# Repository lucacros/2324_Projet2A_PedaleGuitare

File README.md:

# Hi everyone 🖐️ & Welcome to our project: Multi-Effects Guitar Pedal 🎸🎛️

Hello music and technology fans! Welcome to the GitHub showcase for our multi-effects guitar pedal project. Here you'll find details, tools, and resources related to this exciting project. This is an academic project completed in 100 hours by the legendary trio: Luca CROSETTO, Jolan THOMASSET, and Camille LANFREDI

## 📖 Table of contents

- [📌 Présentation](#-présentation)
  - [📅 Management Section](#-management-section)
  - [🛠️ Hardware Section](#-hardware-section)
  - [💻 Software Section](#-software-section)
- [🚀 Contributions](#-contributions)
- [📜 Licence](#-licence)

## 📌 Présentation

Our multi-effects guitar pedal project aims to provide a versatile platform for guitarists, bringing together a variety of sound effects and audio processing tools in a single device. To achieve this, the guitar pedal will feature...

The project is divided into 3 parts: the first one is the project management, the second part is analog part, with the creation of the system's electronic board, and the third is the creation of the various digital audio effects. 
The second is the creation of the various digital audio effects.

## 📅 Management Section

In this section, you'll find everything to do with project management.

[Link to Management.md](Management.md)

## 🛠️ Hardware Section

### Power supply
To obtain these voltage levels, we use several voltage regulators. The first regulator is a switching regulator to go from 12V to 5V and then we use 2 linear regulators to obtain 3.3V and 1.8V. We first use a switching regulator to go from 12V to 5V, because switching regulators are more efficient than linear regulators when the voltage difference between input and output is high. We use linear regulators because they give a very clean output, with a minimum of noise.

We need to supply 2 different voltages: the first +3.3V to supply VDDA (for analogue part) and VDDIO (for Inputs/Outputs) and the second +1.8V to supply VDDD (for digital part).

|   Components   |   Voltages |  Description |
|---    |:-:    |:-    | 
|   VDDIO   |   +3.3V   | Power supply controls the digital I/O levels as well as the output level of LINE outputs. | 
| VDDD   |   +1.8V  | power supply controls the digital I/O levels as well as the output level of LINE outputs   |
|  VDDA  |   +3.3VA   | Power supply is used for the internal analog circuitry including ADC, DAC, LINE inputs, MIC inputs, headphone outputs and reference voltages.|

#### Jack connecting
We use Jack switched for the input and the output of the guitar. The switched Jack allow us to have the choice between a mono-input or a stereo input and a mono-output and a stereo-output. 
When we connect a jack to this connector, the pins SN and TN are disconnected from the pins S and T. It can allow to have 2 connectors to have stereo but still use the 2 input of the codec to have a signal as powerful as a stereo input.
#### Buffer-Button
We use a buffer button to store a part of the sound of the guitar to apply several effects to it. It's one of the several options that offer the granular effect.
When the button is pressed, a signal is sent to the microprocessor. When it receives the signal, the microprocessor stores in the RAM the song it has received for a short time and continuously plays the part stored in the RAM.
#### Potentiometers
We use several potentiometers for all the settings of our effects, the gain, the shape, the reverb ect... All potentiometers are fitted with capacitors to eliminate unwanted noise and high frequencies.

They are 2 versions of the pcb :
| V | Recto | Verso  | Size |
|---|------|-------|-----|
| V1.0|  | | 17 x 10.32 cm |
| V2.0|  | | 10.4 x 9.15 cm |
| V3.0| **WIP**  | **WIP**| 9.71 x 6.76 cm |

As you can see, the first version wasn't optimised. They is a lot of space between components and the design is not very good. That's why we did a new version witch to x2 smaller.

## 💻 Software Section

In this second part you will find everything that concerns the software part of the project. You'll find all the detailed audio effects programs and how they work.

[Link to Software Section](https://github.com/lucacros/2324_Projet2A_PedaleGuitare/tree/Software-Section)

## 🚀 Contributions

We would like to thank each person who helped us and provided support and information, such as:
- M. Nicolas PAPAZOGLOU
- M. Laurent FIACK
- M. Frédéric GERALDO

## 📜 Licence

The project is under the [SI TU VOLES T'ES MORT] license. Refer to the `LICENSE` file for more details.

---
Feel free to star this project (⭐) if you find it interesting!

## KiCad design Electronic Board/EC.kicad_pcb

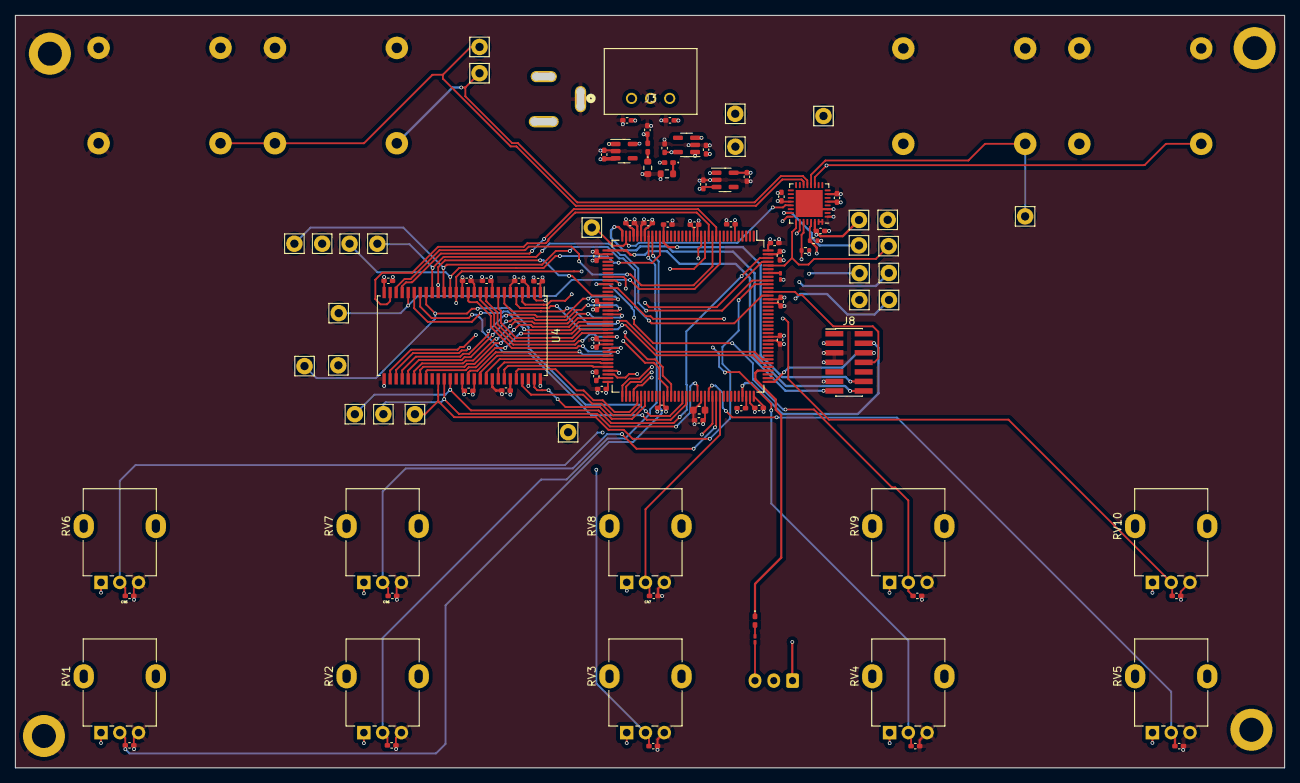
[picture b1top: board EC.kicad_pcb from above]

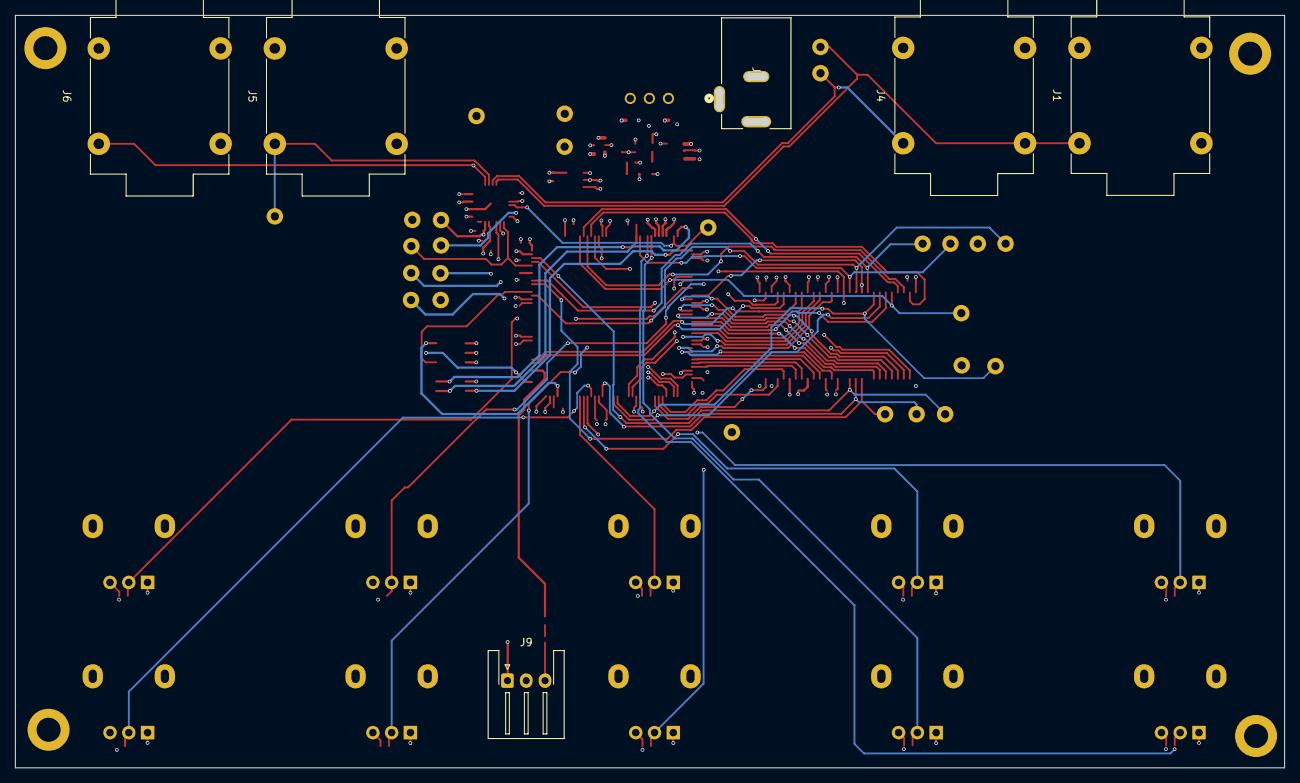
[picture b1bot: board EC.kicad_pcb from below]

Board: 4 copper layers, 169.0 x 100.2 mm, 110 parts (6 on the bottom side), 79 nets.

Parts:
C1: 100uF; C_0402_1005Metric_Pad0.74x0.62mm_HandSolder
C2: 100µF; C_0402_1005Metric_Pad0.74x0.62mm_HandSolder
C3, C4, C5, C6, C7, C8: 1uF; C_0402_1005Metric_Pad0.74x0.62mm_HandSolder
C9, C10, C11, C12, C13, C14, C15, C20, C21, C22, C23, C24, C25, C26, C27, C28, C29, C30, C31, C32, C33, C34, C35, C40, C41, C42, C43, C44, C45, C46, C47, C48, C49, C50, C51, C60: 100nF; C_0402_1005Metric_Pad0.74x0.62mm_HandSolder
C17: 4.7u; C_0603_1608Metric
C18, C19: 2.2uF; C_0402_1005Metric_Pad0.74x0.62mm_HandSolder
D1, D3: RED; LED_0402_1005Metric_Pad0.77x0.64mm_HandSolder
D2: LED; LED_0402_1005Metric_Pad0.77x0.64mm_HandSolder
H1, H2, H3, H4: MountingHole_Pad; MountingHole_3.2mm_M3_DIN965_Pad
J1, J4, J5, J6: NMJ4HCD2; Jack_6.35mm_Neutrik_NMJ4HCD2_Horizontal
J2: 4840.2201; Regulator4840-2201
J3: 173950578; CONN3_950578_WRE_173950578
J8: Conn_02x07_Odd_Even; PinHeader_2x07_P1.27mm_Vertical_SMD
J9: Conn_01x03; JST_XH_S3B-XH-A-1_1x03_P2.50mm_Horizontal
R1, R2: 1k; R_0603_1608Metric
R3: 330; R_0201_0603Metric_Pad0.64x0.40mm_HandSolder
R5, R7: 1.5k; R_0402_1005Metric
R6: 510; R_0201_0603Metric_Pad0.64x0.40mm_HandSolder
RV1, RV2, RV3, RV4, RV5, RV6, RV7, RV8, RV9, RV10: 100k; Potentiometer_Alpha_RD901F-40-00D_Single_Vertical
TP1, TP2, TP3, TP4, TP5, TP6, TP8, TP9, TP10, TP11, TP12, TP13, TP14, TP15, TP16, TP17, TP18, TP19, TP20, TP21, TP22, TP23, TP24, TP25, TP34, TP35: TestPoint; Pin_D1.1mm_L8.5mm_W2.5mm_FlatFork
U1, U2: BU33SD5WG-TR; SOT-23-5
U3: BU18SD2MG-MTR; SOT-23-5
U4: IS42S16400J-xC; TSOP-II-54_22.2x10.16mm_P0.8mm
U6: STM32F446ZCTx; LQFP-144_20x20mm_P0.5mm
U7: SGTL5000XNAA3; QFN-32-1EP_5x5mm_P0.5mm_EP3.6x3.6mm

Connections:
+1V8: C8.1, C51.1, TP4.1, U3.5 (OUT), U7.30 (VDDD)
+3.3V: C4.1, C7.1, C9.1, C10.1, C11.1, C12.1, C13.1, C14.1, C15.1, C17.1, C20.1, C21.1, C22.1, C23.1, C25.1, C26.1, C27.1, C28.1, C29.1, C30.1, C31.1, C32.1, C33.1, C34.1, C35.1, D1.2 (A), J8.3, J9.1, R5.1, R7.1, RV1.1, RV2.1, RV3.1, RV4.1, RV5.1, RV6.1, RV7.1, RV8.1, RV9.1, RV10.1, TP2.1, U1.5 (OUT), U3.1 (IN), U3.3 (STBY), U4.1 (VDD), U4.3 (VDDQ), U4.9 (VDDQ), U4.14 (VDD), U4.27 (VDD), U4.43 (VDDQ), U4.49 (VDDQ), U6.6 (VBAT), U6.17 (VDD), U6.30 (VDD), U6.39 (VDD), U6.52 (VDD), U6.62 (VDD), U6.72 (VDD), U6.84 (VDD), U6.95 (VDDUSB), U6.108 (VDD), U6.121 (VDD), U6.131 (VDD), U6.143 (PDR_ON), U6.144 (VDD), U7.20 (VDDIO)
+3.3VA: C6.1, C24.1, C50.1, D3.2 (A), TP3.1, U2.5 (OUT), U6.33 (VDDA), U7.5 (VDDA)
+5V: C2.1, C3.1, C5.1, J3.3 (Vs), TP1.1, U1.1 (IN), U1.3 (STBY), U2.1 (IN), U2.3 (STBY)
+12V: C1.1, J2.1 (+Ve), J3.1 (+Ve)
/Codec/CK_I2S: TP24.1, U6.74 (PB13), U7.24 (I2S_SCLK)
/Codec/DOUT_I2S: TP22.1, U6.140 (PB9), U7.25 (I2S_DOUT)
/Codec/SCL_I2C: R7.2, TP20.1, U6.69 (PB10), U7.29 (CTRL_CLK)
/Codec/SDA_I2C: R5.2, TP19.1, U6.70 (PB11), U7.27 (CTRL_DATA)
/Codec/SD_I2S: TP21.1, U6.76 (PB15), U7.26 (I2S_DIN)
/Codec/SYS_MCLK: TP18.1, U6.35 (PA1), U7.21 (SYS_MCLK)
/Codec/Ve_guitare_L: J1.T, J4.TN, TP5.1, U7.14 (LINEIN_L)
/Codec/Ve_guitare_R: J4.T, TP34.1, U7.13 (LINEIN_R)
/Codec/Vs_guitare_L: J5.T, TP6.1, U7.12 (LINEOUT_L)
/Codec/Vs_guitare_R: J6.T, TP35.1, U7.11 (LINEOUT_R)
/Codec/WS_I2S: TP23.1, U6.73 (PB12), U7.23 (I2S_LRCLK)
/STM32/A0: TP15.1, U4.23 (A0), U6.10 (PF0)
/STM32/A1: U4.24 (A1), U6.11 (PF1)
/STM32/A2: U4.25 (A2), U6.12 (PF2)
/STM32/A3: U4.26 (A3), U6.13 (PF3)
/STM32/A4: U4.29 (A4), U6.14 (PF4)
/STM32/A5: U4.30 (A5), U6.15 (PF5)
/STM32/A6: U4.31 (A6), U6.50 (PF12)
/STM32/A7: U4.32 (A7), U6.53 (PF13)
/STM32/A8: U4.33 (A8), U6.54 (PF14)
/STM32/A9: U4.34 (A9), U6.55 (PF15)
/STM32/A10: U4.22 (A10), U6.56 (PG0)
/STM32/A11: U4.35 (A11), U6.57 (PG1)
/STM32/BA0: TP25.1, U4.20 (BA0), U6.89 (PG4)
/STM32/BA1: U4.21 (BA1), U6.90 (PG5)
/STM32/D0: TP17.1, U4.2 (DQ0), U6.85 (PD14)
/STM32/D1: U4.4 (DQ1), U6.86 (PD15)
/STM32/D2: U4.5 (DQ2), U6.114 (PD0)
/STM32/D3: U4.7 (DQ3), U6.115 (PD1)
/STM32/D4: U4.8 (DQ4), U6.58 (PE7)
/STM32/D5: U4.10 (DQ5), U6.59 (PE8)
/STM32/D6: U4.11 (DQ6), U6.60 (PE9)
/STM32/D7: U4.13 (DQ7), U6.63 (PE10)
/STM32/D8: U4.42 (DQ8), U6.64 (PE11)
/STM32/D9: U4.44 (DQ9), U6.65 (PE12)
/STM32/D10: U4.45 (DQ10), U6.66 (PE13)
/STM32/D11: U4.47 (DQ11), U6.67 (PE14)
/STM32/D12: U4.48 (DQ12), U6.68 (PE15)
/STM32/D13: U4.50 (DQ13), U6.77 (PD8)
/STM32/D14: U4.51 (DQ14), U6.78 (PD9)
/STM32/D15: U4.53 (DQ15), U6.79 (PD10)
/STM32/NBL0: TP14.1, U4.15 (LDQM), U6.141 (PE0)
/STM32/NBL1: TP16.1, U4.39 (UDQM), U6.142 (PE1)
/STM32/SDCKE1: TP9.1, U4.37 (CKE), U6.135 (PB5)
/STM32/SDCLK: TP8.1, U4.38 (CLK), U6.93 (PG8)
/STM32/SDNCAS: TP13.1, U4.17 (~CAS), U6.132 (PG15)
/STM32/SDNE1: TP10.1, U4.19 (~CS), U6.136 (PB6)
/STM32/SDNRAS: TP11.1, U4.18 (~RAS), U6.49 (PF11)
/STM32/SDNWE: TP12.1, U4.16 (~WE), U6.26 (PC0)
GND: C1.2, C2.2, C3.2, C4.2, C5.2, C6.2, C7.2, C8.2, C9.2, C10.2, C11.2, C12.2, C13.2, C14.2, C15.2, C17.2, C18.2, C19.2, C20.2, C21.2, C22.2, C23.2, C24.2, C25.2, C26.2, C27.2, C28.2, C29.2, C30.2, C31.2, C32.2, C33.2, C34.2, C35.2, C40.2, C41.2, C42.2, C43.2, C44.2, C45.2, C46.2, C47.2, C48.2, C49.2, C50.2, C51.2, C60.2, H1.1, H2.1, H3.1, H4.1, J1.S, J1.SN, J1.TN, J2.3 (GND), J3.2 (GND), J4.S, J4.SN, J5.S, J5.SN, J6.S, J6.SN, J8.5, J8.7, J8.11, R1.2, R2.2, R6.1, RV1.3, RV2.3, RV3.3, RV4.3, RV5.3, RV6.3, RV7.3, RV8.3, RV9.3, RV10.3, U1.2 (GND), U2.2 (GND), U3.2 (GND), U4.6 (GNDQ), U4.12 (GNDQ), U4.28 (GND), U4.41 (GND), U4.46 (GNDQ), U4.52 (GNDQ), U4.54 (GND), U6.16 (VSS), U6.31 (VSSA), U6.32 (VREF+), U6.38 (VSS), U6.51 (VSS), U6.61 (VSS), U6.83 (VSS), U6.94 (VSS), U6.107 (VSS), U6.120 (VSS), U6.130 (VSS), U7.1 (GND), U7.3 (GND), U7.7 (AGND), U7.31 (CTRL_ADR0_CS), U7.32 (CTRL_MODE), U7.33 (GND)
NRST: C60.1, J8.12, U6.25 (NRST)
unnamed: D1.1 (K), R1.1
unnamed: D2.2 (A), R3.1
unnamed: D2.1 (K), U6.112 (PC11)
unnamed: D3.1 (K), R2.1
unnamed: J9.3, R3.2
unnamed: R6.2, U6.138 (BOOT0)
unnamed: C18.1, U6.71 (VCAP_1)
unnamed: C19.1, U6.106 (VCAP_2)
Pot_0: C40.1, RV1.2, U6.28 (PC2)
Pot_1: C41.1, RV2.2, U6.29 (PC3)
Pot_2: C42.1, RV3.2, U6.44 (PC4)
Pot_3: C43.1, RV4.2, U6.45 (PC5)
Pot_4: C44.1, RV5.2, U6.96 (PC6)
Pot_5: C45.1, RV6.2, U6.97 (PC7)
Pot_6: C46.1, RV7.2, U6.98 (PC8)
Pot_7: C47.1, RV8.2, U6.99 (PC9)
Pot_8: C48.1, RV9.2, U6.46 (PB0)
Pot_9: C49.1, RV10.2, U6.47 (PB1)
SWCLK: J8.6, U6.109 (PA14)
SWDIO: J8.4, U6.105 (PA13)
SWO: J8.8, U6.133 (PB3)
USART2_RX: J8.13, U6.37 (PA3)
USART2_TX: J8.14, U6.36 (PA2)

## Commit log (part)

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2023-11-07 Update Simplereverb.md
    OMG
2023-11-07 Update README.md
    fixs
2023-11-14 Update README.md
    download in c
2023-12-01 Create UserManual
2023-12-12 Update README.md
    Distorsion results
2023-12-16 Create Routing_Table
2023-12-16 Update Routing_Table
2023-12-26 Add files via upload
    This is the STM32CubeIDE project with the simple distorsion effect
2024-01-16 16/01/24 Work
2024-01-16 Delete Sound card CODEC project.zip
    Update, PME.zip
2024-01-23 test effect in cpp
2024-01-23 update stm32 file, 23/01
2024-01-30 Work 30/01
2024-02-06 Datasheet of the nucleo card
    for the potentiometer pins
2024-02-06 Work session 06/02/24
2024-02-12 Distorsion Effect Update
2024-02-16 Create delaycodes
2024-02-27 Create Pedal-3D-Box
2024-02-27 Rename Pedal-3D-Box to Pedal-3D-Box.md
2024-02-27 séance du 27/02/24
2024-03-05 Rename faustdistorsion.c to faustdistorsionexported.c
